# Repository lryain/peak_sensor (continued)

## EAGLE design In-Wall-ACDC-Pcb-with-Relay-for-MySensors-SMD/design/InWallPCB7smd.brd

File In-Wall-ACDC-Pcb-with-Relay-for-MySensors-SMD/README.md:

This is a PCB that uses AC power to run a MySensors node and a relay (SSR) inside a wall socket. The main goal is to have a MySensors node with I/O to be able to build your own node with your own sensors inside a normal (European) wall socket. It comes with PCB and a 3d box for protection and safety. 

This is a development of my first [In-Wall-ACDC-Pcb-for-MySensors](https://www.openhardware.io/view/13/In-Wall-ACDC-Pcb-for-MySensors) (Not SMD components, only axial)

_Note: This PCB are using SMD components!_

### Current Status and revision

Working on rev 7.1 including MysX 2.?, security improvements
Sent to PCB house 16sept, testing next.

#### Rev 7.0

- Changes in resistors and NPN transistor for relay to work better.
- Designed 3dboxes for safety.
- Increased AC-DC separation (Rev 7 = 5mm)
- AC clearance 2.5mm minimum, added millings.
- Redesigned outer dimension/border.
- Safety recommendations: This PCB meets the criteria of pollution level II (2,5mm (Basic) AC seperation and 5mm (Reinforced) AC-DC separation ) and can be used "where only non-conductive contamination occurs. However, occasional temporary conductivity must be expected as a result of moisture condensation." To be on the safe side - use a sealed case!

_For rev history, see Changes.txt_

_Note when buying through openhardware.io may say another rev. This is only revision for manufacturer, not current PCB revision. I always update PCB gerber files for sale first on openhardware.io_

### **Why??**

I designed this project for the main purpose of safely powering a node from a AC source. Battery operations and 5v phone chargers in all its glory but I needed a node small enough to put inside a wall-socket, adaptable/dynamic and AC powered. 

We have AC mains running everywhere in our houses today and this project aims for converting AC to 5vDC with safety as priority #1. 

#### Aim of this project

- Convert 240v/120v AC to 5v DC (using HLK-PM01)

- Make it safe!

- Fit inside standard [appliance box](http://www.elko.se/getfile.php/produkter/img/3/3/4944/Foto4944.jpg) / in wall

- Run MySensors node (Arduino Pro Mini, NRF24L01+, MysX Gpio for sensors)

- Have a on board relay (SSR).

- Make it as small as possible using SMD components.

### **How??**

By using this you have everything you need for a AC powered MySensors node. With MysX connector you have plenty of options both digital and analog input/outputs for you sensors. For the AC power there are both a temperature fuse, a normal fuse, and a varistor to protect your node.

I wanted the node to be dynamic (no sensor specific) - and therefore the MysX connector. Now you can add any sensor you like to the connector. Also, while at it - why not add a relay. Since Im going to use this around AC i might also be able to switch it in the same time.

Follow this thread for latest info: https://forum.mysensors.org/topic/4187/in-wall-pcb-with-relay-for-mysensors-smd

Build instructions coming soon, see BOM for more info.

### **What??**

**Power **- Using the HLK-PM01 converting AC 240/120v to 5v dc and running the MySensors node. The input is protected with a fuse, temp fuse and varistor ([read this discussion](http://forum.mysensors.org/topic/1607/safe-in-wall-ac-to-dc-transformers)).

**MySensors **- A Atmega328p-au (normal schematics) and a Nrf24l01+ SMD Radio with all the normal components.

**I/O** - MysX (Raw input not possible) + some extra (A4+A5), ICSP**

**Relay(SSR)** - A Omron G3MC-202PL protected with a fuse of your choise (axial)

**3d-box** - A part of safety, attached is a .stl file with a case for 3d printing. This can be printed in your 3d printer or sent to a 3d-hub.

### Safety

Safety is one of the most important aspects of this project! Se more here: https://forum.mysensors.org/topic/4175/clearance-creepage-and-other-safety-aspects-in-mysensors-pcbs. It is highly recommended to use the latest revision for best safety.

Text below is written for the latest posted revision. For older revisions, please see changes.txt

##### AC-DC Separation
My thoughts has been to separate AC (primary) and DC (secondary) sides completely. At this point (Rev 7.0) this separation is 6.5mm so below minimum for use outdoor (in pollution level 3 = 8.0mm) but it should be OK if you dont use in in worst case pollution. In upcoming revisions I may add millings to increase creepage. This revision i recommend using it indoors and with the 3d case (or any case!) If you put it in a completely sealed case it should be ok to use outdoor.

The HLK-PM01 has been discussed in many threads here and are transformer based so it should be safe. More about it [here ](http://lygte-info.dk/review/Power%20Mains%20to%205V%200.6A%20Hi-Link%20HLK-PM01%20UK.html)and [here](https://skippy.org.uk/quick-look-at-the-hlk-pm01/).  

Note: there has recently (Sept 16) been some [fake/pirated HLK components](https://forum.mysensors.org/topic/1607/safe-in-wall-ac-to-dc-transformers/356)! Warning!

##### AC high voltage trace creepage

As for the separation within the AC traces I have tried to use 3mm creepage and clearance but this turned out to be to hard. This PCB  (Rev 7.0) has a creepage distance on the AC side of 2.5mm. This means if you are using 240v you can put it in pollution level II Sames as above, dont use it outdoors and put it in a case.

### Disclaimer

If you order or use this you agree to and understand that the author is not liable for any injury or damage howsoever caused and that you use this PCB at your own risk. This is DIY and the author has not made any professional test. This product has not been marked with any certification marks and cant be guaranteed to compliance with any standards. 

### **Cost**?
Total cost for one node is about US$14 where the relay and HLK-pm01 is about US$10(See BOM).

### **Bonus**

You can actually cut/split the PCB between AC and DC side and get a normal 5v MySensors node where you can attach sensors to MysX connector.

##### Links

- http://forum.mysensors.org/topic/1607/safe-in-wall-ac-to-dc-transformers

- http://forum.mysensors.org/topic/1540/110v-230v-ac-to-mysensors-pcb-board

- [Performance test and review of mains to 5V 0.6A Hi-Link HLK-PM01](http://lygte-info.dk/review/Power%20Mains%20to%205V%200.6A%20Hi-Link%20HLK-PM01%20UK.html)

- https://skippy.org.uk/quick-look-at-the-hlk-pm01/

- https://www.ieee.li/pdf/essay/safety_considerations_in_power_supply_design.pdf

### Questions needing answers

- Reliability, when will it fail? (compared to a commercial product?)
- How will it fail? What is it weakest point?
- Will my safety components be enough and prevail damage... ?
- What will happen when it fails?

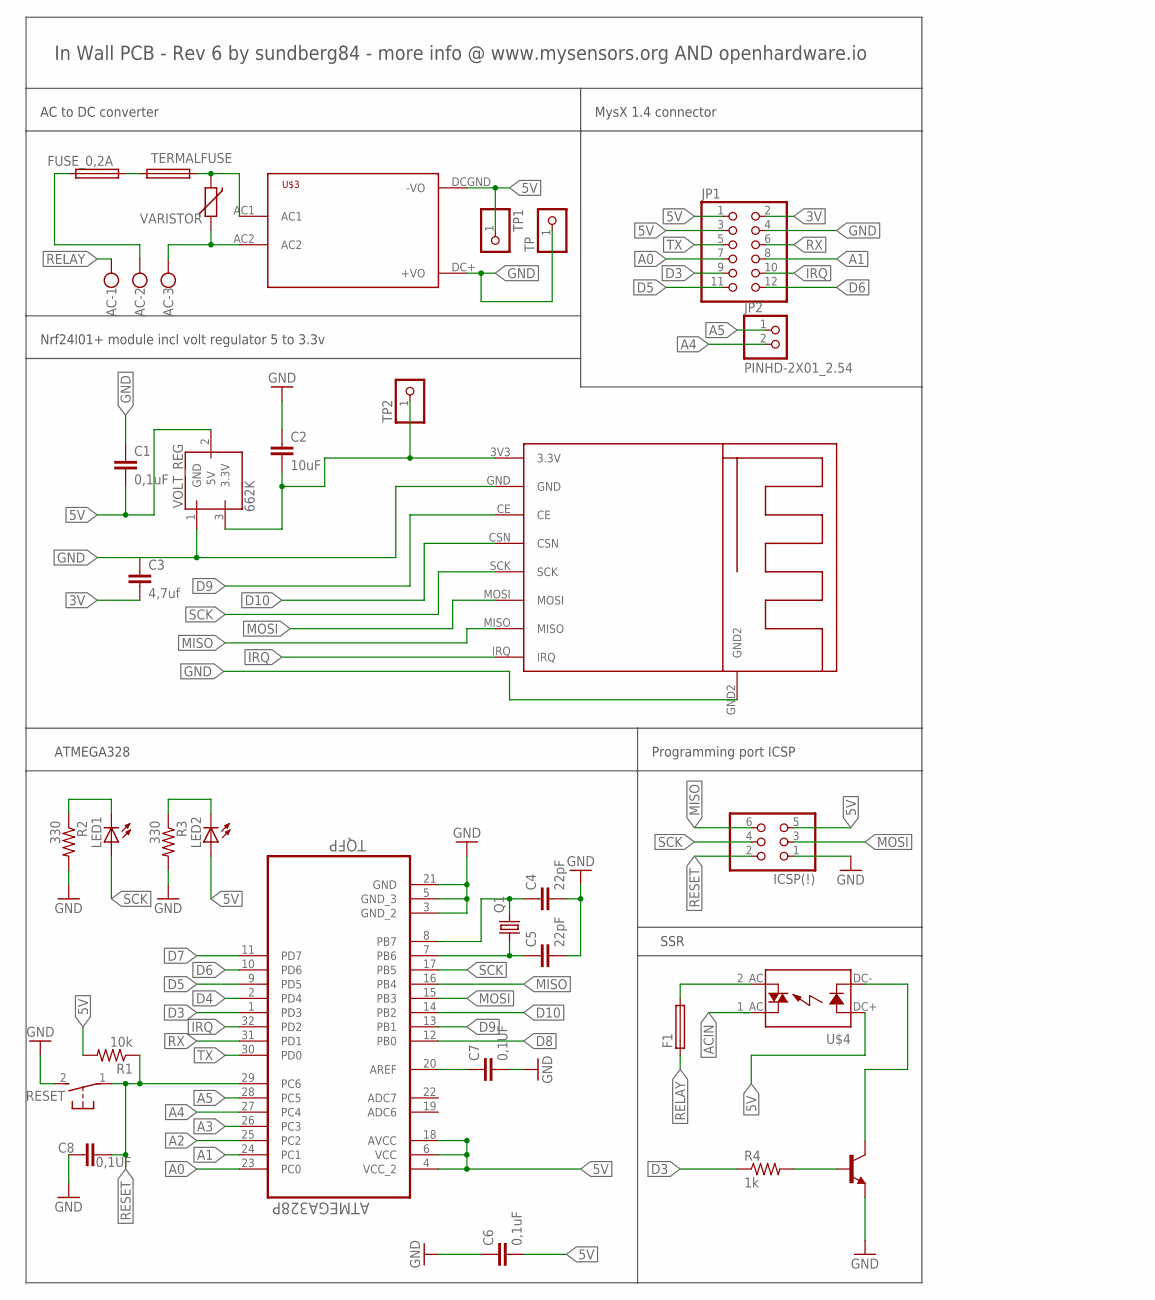
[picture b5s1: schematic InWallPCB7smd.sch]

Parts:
AC: W237-103
ATMEGA328: ATMEGA328P-AU; QFP80P900X900X120-32N
C1, C6: 0,1uF; 0805
C2: 10uF; 0805
C3: 4,7uf; 0805
C4, C5: 22pF; 0805
C7, C8: 0,1UF; 0805
F1: 19559
FUSE_0,2A: FUSETE5; TE5
ICSP(!): PINHD-2X03_2.54; 2X03
J3Y: J3Y_S8050_SMD_NPN_TRANSISTOR; SOT-23-3
JP1: PINHD-2X06_2.54; 2X06
JP2: PINHD-2X01_2.54; 2X01
LED1, LED2: LEDCHIPLED_0805; CHIPLED_0805
Q1: CRYSTALHC49S; HC49/S
R1: 10k; 0805
R2, R3: 330; 0805
R4: 1k; 0805
RESET: DTSM-3
TERMALFUSE: FUSETE5; TE5
TP, TP1, TP2: PINHD-1X1; 1X01
U$1: SMD24L01+SMD; NRF24L01+SMD
U$3: HLK-PM01
U$4: OMRON_G3MC-202PL_5V_SSR; OMRON_G3MC_202PL_5V_SSR
VARISTOR: VARISTOR-7,5; R-7,5
VOLT_REG: 662K; SOT-23-3

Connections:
3V: C2.2, C3.2, JP1.2, TP2.1, U$1.3V3 (3.3V), VOLT_REG.3 (3.3V)
5V: ATMEGA328.4 (VCC_2), ATMEGA328.6 (VCC), ATMEGA328.18 (AVCC), C1.2, C6.2, ICSP(!).5, JP1.1, JP1.3, LED2.A, R1.2, TP1.1, U$3.DCGND (-VO), U$4.DC+ (DCSIGNAL), VOLT_REG.2 (5V)
A0: ATMEGA328.23 (PC0), JP1.7
A1: ATMEGA328.24 (PC1), JP1.8
A2: ATMEGA328.25 (PC2)
A3: ATMEGA328.26 (PC3)
A4: ATMEGA328.27 (PC4), JP2.2
A5: ATMEGA328.28 (PC5), JP2.1
ACGND: AC.3, U$3.AC2, VARISTOR.2
ACIN: AC.2, FUSE_0,2A.1, U$4.1_AC (HOT)
D3: ATMEGA328.1 (PD3), JP1.9, R4.1
D4: ATMEGA328.2 (PD4)
D5: ATMEGA328.9 (PD5), JP1.11
D6: ATMEGA328.10 (PD6), JP1.12
D7: ATMEGA328.11 (PD7)
D8: ATMEGA328.12 (PB0)
D9: ATMEGA328.13 (PB1), U$1.CE
D10: ATMEGA328.14 (PB2), U$1.CSN
GND: ATMEGA328.3 (GND_2), ATMEGA328.5 (GND_3), ATMEGA328.21 (GND), C1.1, C2.1, C3.1, C4.2, C5.2, C6.1, C7.2, C8.1, ICSP(!).1, J3Y.3 (E), JP1.4, R2.2, R3.2, RESET.2, TP.1, U$1.GND, U$1.GND2, U$3.DC+ (+VO), VOLT_REG.1 (GND)
IRQ: ATMEGA328.32 (PD2), JP1.10, U$1.IRQ
MISO: ATMEGA328.16 (PB4), ICSP(!).6, U$1.MISO
MOSI: ATMEGA328.15 (PB3), ICSP(!).3, U$1.MOSI
unnamed: FUSE_0,2A.2, TERMALFUSE.2
unnamed: LED1.C, R2.1
unnamed: F1.2, U$4.2_AC (NEUTRAL)
unnamed: ATMEGA328.8 (PB7), C4.1, Q1.2
unnamed: LED2.C, R3.1
unnamed: TERMALFUSE.1, U$3.AC1, VARISTOR.1
unnamed: ATMEGA328.7 (PB6), C5.1, Q1.1
unnamed: ATMEGA328.20 (AREF), C7.1
unnamed: J3Y.1 (B), R4.2
unnamed: J3Y.2 (C), U$4.DC- (DCGND)
RELAY: AC.1, F1.1
RESET: ATMEGA328.29 (PC6), C8.2, ICSP(!).2, R1.1, RESET.1
RX: ATMEGA328.31 (PD1), JP1.6
SCK: ATMEGA328.17 (PB5), ICSP(!).4, LED1.A, U$1.SCK
TX: ATMEGA328.30 (PD0), JP1.5

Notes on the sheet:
AC to DC converter
Nrf24l01+ module incl volt regulator 5 to 3.3v
MysX 1.4 connector
In Wall PCB - Rev 6 by sundberg84 - more info @ www.mysensors.org AND openhardware.io
Programming port ICSP
ATMEGA328
SSR

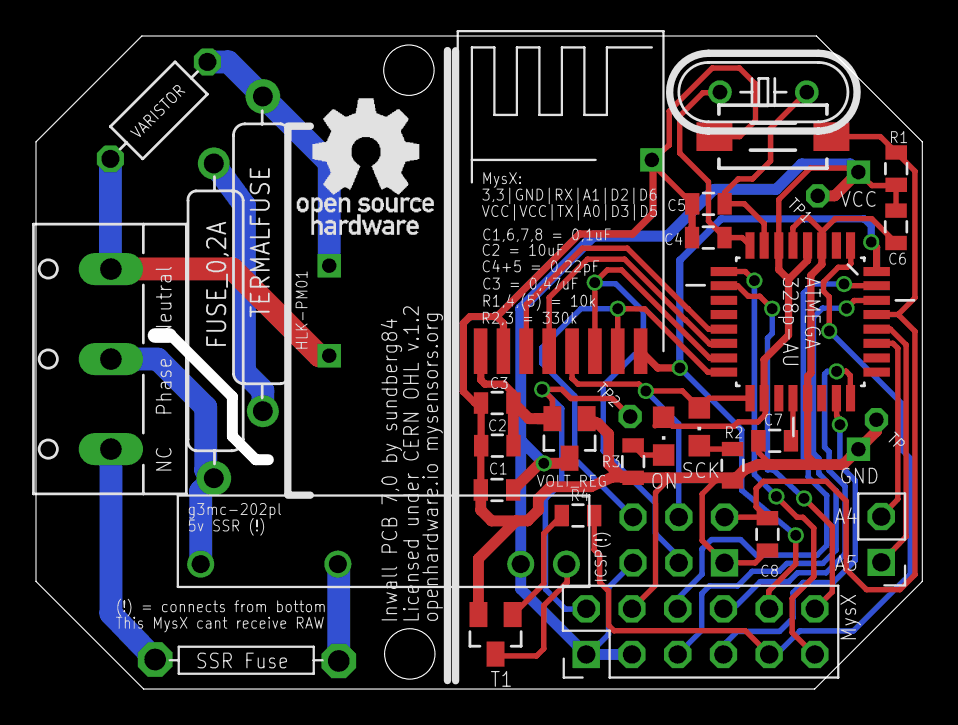
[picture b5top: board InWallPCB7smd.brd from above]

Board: 2 copper layers, 49.2 x 36.3 mm, 33 parts (1 on the bottom side), 32 nets.

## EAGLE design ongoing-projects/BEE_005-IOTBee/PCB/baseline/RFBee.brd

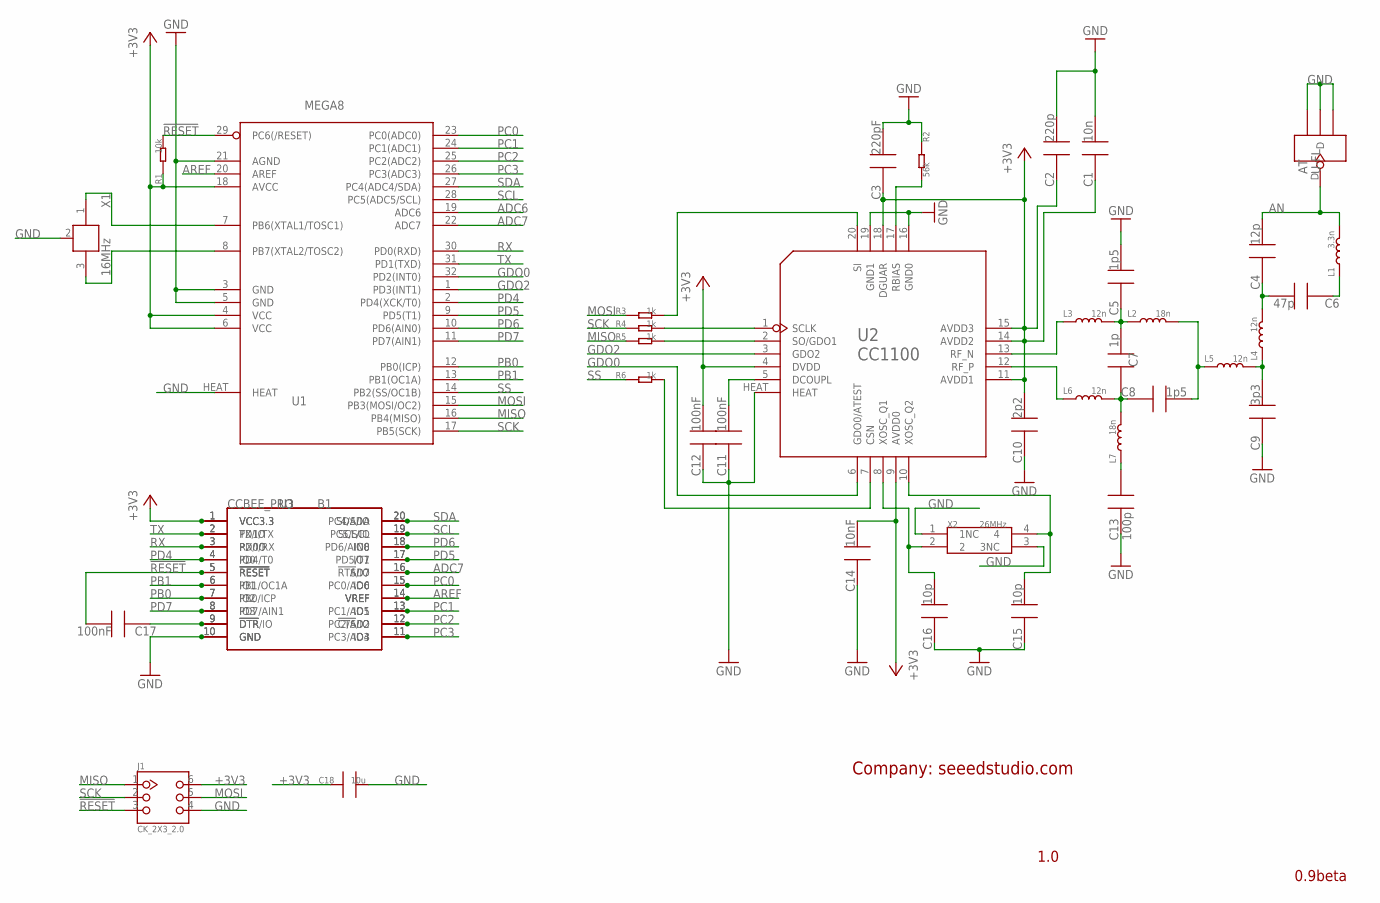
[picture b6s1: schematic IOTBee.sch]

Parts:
AT: U-FL
B1: CCBEE_PRO; CCBEE-PRO
C1: 10n; 0603_S
C2: 220p; 0603_S
C3: 220pF; 0603_S
C4: 12p; 0603_S
C5, C8: 1p5; 0603_S
C6: 47p; 0603_S
C7: 1p; 0603_S
C9: 3p3; 0603_S
C10: 2p2; 0603_S
C11, C12, C17: 100nF; 0603_S
C13: 100p; 0603_S
C14: 10nF; 0603_S
C15, C16: 10p; 0603_S
C18: 10u; 0805
J1: CK_2X3_2.0
L1: 3.3n; 0603_S
L2, L7: 18n; 0603_S
L3, L4, L5, L6: 12n; 0603_S
R1: 10k; 0603_S
R2: 56k; 0603_S
R3, R4, R5, R6: 1k; 0603_S
U1: MEGA8; MLF32X
U2: CC1100; QFN20
U3: BEE-OPENBEE-BTSMD; 20P-SMD-2.0-BT
X1: 16MHz; XTAL_3X2
X2: 26MHz; X3225

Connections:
!RESET: B1.5 (!RESET), C17.2, J1.3, R1.2, U1.29 (PC6(/RESET)), U3.5 (!RESET)
+3V3: B1.1 (VCC3.3), C1.1, C2.1, C3.1, C10.2, C12.2, C14.2, C18.1, J1.6, R1.1, U1.4 (VCC), U1.6 (VCC), U1.18 (AVCC), U2.4 (DVDD), U2.9 (AVDD0), U2.11 (AVDD1), U2.14 (AVDD2), U2.15 (AVDD3), U2.18 (DGUAR), U3.1 (VCC3.3)
ADC6: U1.19 (ADC6)
ADC7: B1.16 (AD7), U1.22 (ADC7), U3.16 (!RTS!/IO)
AN: AT.D, C4.2, L1.2
AREF: B1.14 (VREF), U1.20 (AREF), U3.14 (VREF)
DTR: B1.9 (!DTR), C17.1, U3.9 (!DTR!/IO)
GDO0: U1.32 (PD2(INT0)), U2.6 (GDO0/ATEST)
GDO2: U1.1 (PD3(INT1)), U2.3 (GDO2)
GND: AT.GND1, AT.GND2, AT.GND3, B1.10 (GND), C1.2, C2.2, C3.2, C5.2, C9.1, C10.1, C11.1, C12.1, C13.1, C14.1, C15.1, C16.1, C18.2, J1.4, R2.1, U1.3 (GND), U1.5 (GND), U1.21 (AGND), U1.HEAT, U2.16 (GND0), U2.19 (GND1), U2.HEAT, U3.10 (GND), X1.2 (GND), X2.1 (1NC), X2.3 (3NC)
MISO: J1.1, R5.1, U1.16 (PB4(MISO))
MOSI: J1.5, R3.1, U1.15 (PB3(MOSI/OC2))
unnamed: C11.2, U2.5 (DCOUPL)
unnamed: C16.2, U2.8 (XOSC_Q1), X2.2
unnamed: R4.2, U2.1 (SCLK)
unnamed: L3.1, U2.13 (RF_N)
unnamed: L6.1, U2.12 (RF_P)
unnamed: C5.1, C7.2, L2.1, L3.2
unnamed: C7.1, C8.1, L6.2, L7.2
unnamed: C8.2, L2.2, L5.1
unnamed: C9.2, L4.1, L5.2
unnamed: C4.1, C6.2, L4.2
unnamed: U1.7 (PB6(XTAL1/TOSC1)), X1.1
unnamed: C13.2, L7.1
unnamed: U1.8 (PB7(XTAL2/TOSC2)), X1.3 (2)
unnamed: R3.2, U2.20 (SI)
unnamed: R2.2, U2.17 (RBIAS)
unnamed: C15.2, U2.10 (XOSC_Q2), X2.4
unnamed: R5.2, U2.2 (SO/GDO1)
unnamed: R6.2, U2.7 (CSN)
unnamed: C6.1, L1.1
PB0: B1.7 (PB0/ICP), U1.12 (PB0(ICP)), U3.7 (IO2)
PB1: B1.6 (PB1/OC1A), U1.13 (PB1(OC1A)), U3.6 (IO1)
PC0: B1.15 (PC0/AD0), U1.23 (PC0(ADC0)), U3.15 (IO6)
PC1: B1.13 (PC1/AD1), U1.24 (PC1(ADC1)), U3.13 (IO5)
PC2: B1.12 (PC2/AD2), U1.25 (PC2(ADC2)), U3.12 (!CTS!/IO)
PC3: B1.11 (PC3/AD3), U1.26 (PC3(ADC3)), U3.11 (IO4)
PD4: B1.4 (PD4/T0), U1.2 (PD4(XCK/T0)), U3.4 (IO0)
PD5: B1.17 (PD5/T1), U1.9 (PD5(T1)), U3.17 (IO7)
PD6: B1.18 (PD6/AIN0), U1.10 (PD6(AIN0)), U3.18 (IO8)
PD7: B1.8 (PD7/AIN1), U1.11 (PD7(AIN1)), U3.8 (IO3)
RX: B1.3 (PD0/RX), U1.30 (PD0(RXD)), U3.3 (RX/IO)
SCK: J1.2, R4.1, U1.17 (PB5(SCK))
SCL: B1.19 (PC5/SCL), U1.28 (PC5(ADC5/SCL)), U3.19 (SCL/IO)
SDA: B1.20 (PC4/SDA), U1.27 (PC4(ADC4/SDA)), U3.20 (SDA/IO)
SS: R6.1, U1.14 (PB2(SS/OC1B))
TX: B1.2 (PD1/TX), U1.31 (PD1(TXD)), U3.2 (TX/IO)

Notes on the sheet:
0.9beta
1.0
Company: seeedstudio.com

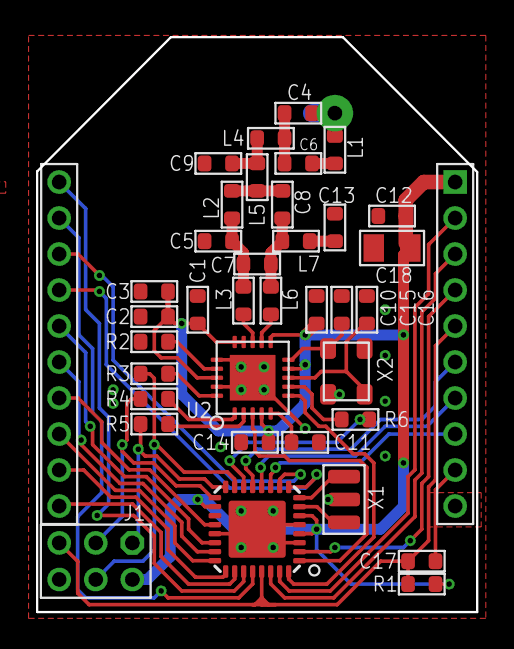
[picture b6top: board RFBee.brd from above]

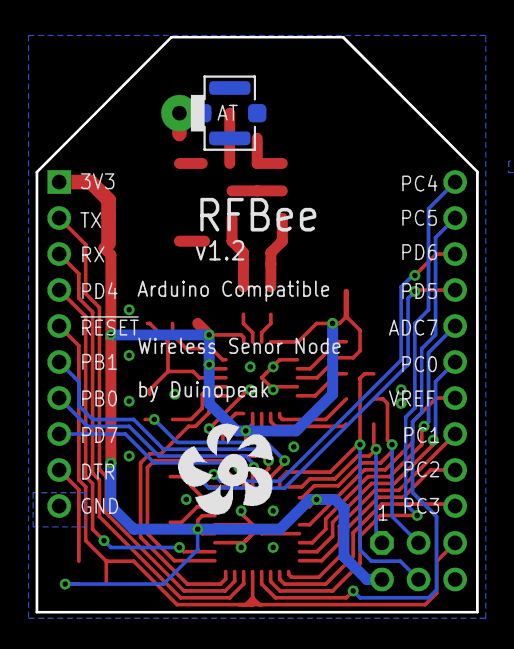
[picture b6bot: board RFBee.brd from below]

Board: 2 copper layers, 24.4 x 31.9 mm, 39 parts (3 on the bottom side), 46 nets.

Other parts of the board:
U$1: DUINOFUN-LOGO-PCB-0.7

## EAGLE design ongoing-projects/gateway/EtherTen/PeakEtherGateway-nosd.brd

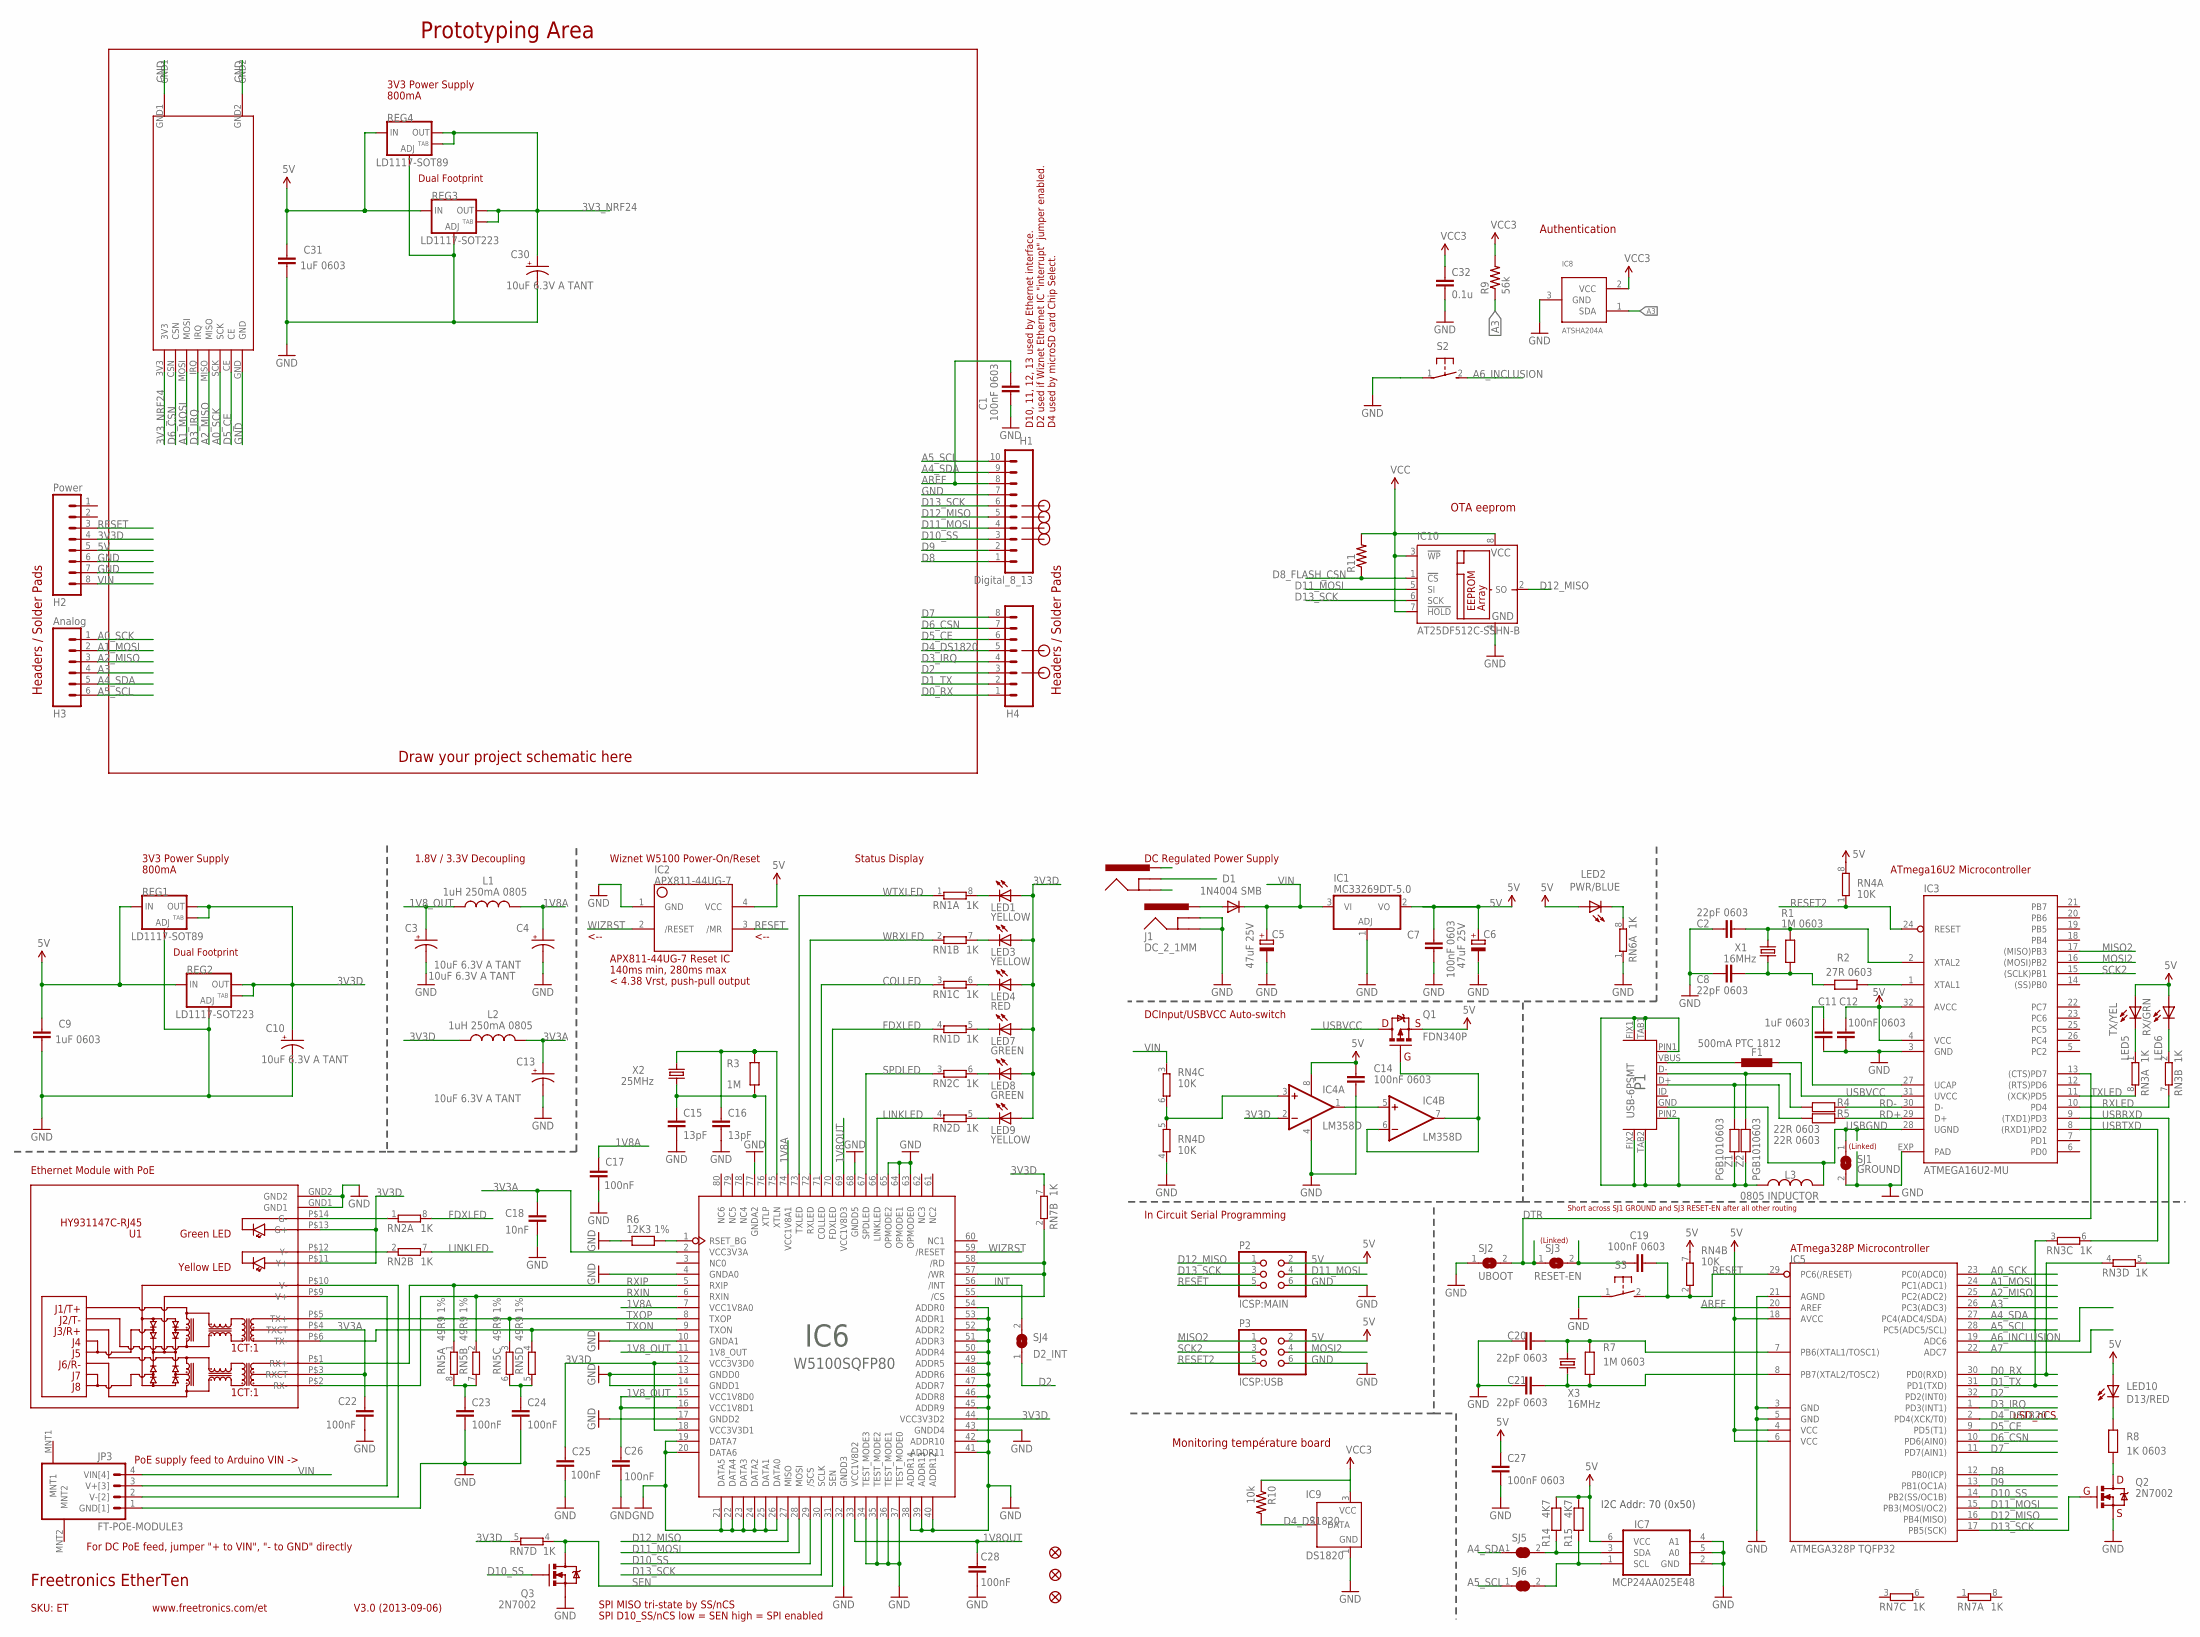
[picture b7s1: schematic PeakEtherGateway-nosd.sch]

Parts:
C1, C7, C12, C14, C19, C27: 100nF 0603; 0603
C2, C8, C20, C21: 22pF 0603; 0603
C3, C4, C10, C13, C30: 10uF 6.3V A TANT; EIA3216
C5, C6: 47uF 25V; PANASONIC_D
C9, C11, C31: 1uF 0603; 0603
C15, C16: 13pF; 0603
C17, C22, C23, C24, C25, C26, C28: 100nF; 0603
C18: 10nF; 0603
C32: 0.1u; 0603-CAP
D1: 1N4004 SMB; SMB-DIODE
F1: 500mA PTC 1812; L1812
FID1, FID2, FID3: FIDUCIAL1X2.5; FIDUCIAL-1X2.5
H1: Digital_8_13; 1X10
H2: Power; 1X08
H3: Analog; 1X06
H4: Digital_0_7; 1X08
IC1: MC33269DT-5.0; DPACK
IC2: APX811-44UG-7; SOT143-R
IC3: ATMEGA16U2-MU; ATMEL_QFN32
IC4: LM358D; SO08
IC5: ATMEGA328P TQFP32; TQFP32-08
IC6: W5100SQFP80; SQFP80
IC7: MCP24AA025E48; SOT23-6
IC8: ATSHA204A; SOT23
IC9: DS1820; TO92-
IC10: AT25DF512C-SSHN-B; SO-08
J1: DC_2_1MM; POWER_JACK_PTH
J2: POWER_JACKOVERPASTE_REDBOARD_0603; POWER_JACK_SMD_OVERPASTE_REDBOARD_0603
JP3: FT-POE-MODULE3; FT-POE-MODULE-NOLABEL
L1, L2: 1uH 250mA 0805; L2012C
L3: 0805 INDUCTOR; 0805-LARGE
LED1, LED3, LED9: YELLOW; LED-0603
LED2: PWR/BLUE; LED-0603
LED4: RED; LED-0603
LED5: TX/YEL; LED-0603
LED6: RX/GRN; LED-0603
LED7, LED8: GREEN; LED-0603
LED10: D13/RED; LED-0603
P1: USB-6PSMT; USB-MICROB-MB05PMXX
P2: ICSP:MAIN; 2X03
P3: ICSP:USB; 2X03
Q1: FDN340P; SOT23
Q2, Q3: 2N7002; SOT23-3
R1, R7: 1M 0603; 0603
R2: 27R 0603; 0603
R3: 1M; 0603
R4, R5: 22R 0603; 0603
R6: 12K3 1%; 0603
R8: 1K 0603; 0603
R9: 56k; 0603-RES
R10: 10k; 0603-RES
R11: RESISTOR0603-RES; 0603-RES
R14, R15: 4K7; 0603
REG1, REG4: LD1117-SOT89; SOT89
REG2, REG3: LD1117-SOT223; SOT223
RN1, RN2, RN3, RN6, RN7: 1K; CAY16
RN4: 10K; CAY16
RN5: 49R9 1%; CAY16
S2, S3: 31-XX; B3F-31XX
SJ1: GROUND; SJ
SJ2: UBOOT; SJ
SJ3: RESET-EN; SJ
SJ4: D2_INT; SJ
SJ5, SJ6: SJCN; SJC
U1: HY931147C-RJ45; HY931147C
U$17: NRF2401; NRF2401_PA_OUTLINE
X1, X3: 16MHz; HC49U-V
X2: 25MHz; HC49U-V
Z1, Z2: PGB1010603; 0603

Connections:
1V8A: C4.A (+), C17.1, IC6.7 (VCC1V8A0), IC6.74 (VCC1V8A1), L1.2
1V8OUT: C28.1, IC6.33 (VCC1V8D2), IC6.69 (VCC1V8D3)
1V8_OUT: C3.A (+), C26.1, IC6.11 (1V8_OUT), IC6.15 (VCC1V8D0), IC6.16 (VCC1V8D1), L1.1
3V3A: C13.A (+), C18.1, C22.1, IC6.2 (VCC3V3A), L2.2, U1.P$3 (RXCT), U1.P$4 (TXCT)
3V3D: C10.A (+), C25.1, H2.4, IC4.2 (-IN), IC6.12 (VCC3V3D0), IC6.18 (VCC3V3D1), IC6.44 (VCC3V3D2), L2.1, LED1.A, LED3.A, LED4.A, LED7.A, LED8.A, LED9.A, REG1.2 (OUT), REG1.4 (OUT), REG2.2 (OUT), REG2.4 (OUT), RN7.5 (2), RN7.7 (2), U1.P$11 (Y+), U1.P$13 (G+)
3V3_NRF24: C30.A (+), C32.1, IC8.2 (VCC), IC9.3 (VCC), IC10.3 (!WP), IC10.7 (!HOLD), IC10.8 (VCC), R9.2, R10.1, R11.2, REG3.2 (OUT), REG3.4 (OUT), REG4.2 (OUT), REG4.4 (OUT), U$17.3V3
5V: C6.+, C7.1, C9.1, C12.1, C14.1, C27.1, C31.1, H2.5, IC1.2 (VO), IC2.4 (VCC), IC3.4 (VCC), IC3.32 (AVCC), IC4.8 (V+), IC5.4 (VCC), IC5.6 (VCC), IC5.18 (AVCC), IC7.6 (VCC), LED2.A, LED5.A, LED6.A, LED10.A, P2.2, P3.2, Q1.2 (S), R14.1, R15.1, REG1.3 (IN), REG2.3 (IN), REG3.3 (IN), REG4.3 (IN), RN4.7 (2), RN4.8 (2)
A0_SCK: H3.1, IC5.23 (PC0(ADC0)), U$17.SCK
A1_MOSI: H3.2, IC5.24 (PC1(ADC1)), U$17.MOSI
A2_MISO: H3.3, IC5.25 (PC2(ADC2)), U$17.MISO
A3: H3.4, IC5.26 (PC3(ADC3)), IC8.1 (SDA), R9.1
A4_SDA: H1.9, H3.5, IC5.27 (PC4(ADC4/SDA)), SJ5.1
A5_SCL: H1.10, H3.6, IC5.28 (PC5(ADC5/SCL)), SJ6.1
A6_INCLUSION: IC5.19 (ADC6), S2.2 (S)
A7: IC5.22 (ADC7)
AREF: C1.1, H1.8, IC5.20 (AREF)
COLLED: IC6.71 (COLLED), RN1.3 (1)
D0_RX: H4.1, IC5.30 (PD0(RXD)), RN3.4 (1)
D1_TX: H4.2, IC5.31 (PD1(TXD)), RN3.3 (1)
D2: H4.3, IC5.32 (PD2(INT0)), SJ4.1
D3_IRQ: H4.4, IC5.1 (PD3(INT1)), U$17.IRQ
D4_DS1820: H4.5, IC5.2 (PD4(XCK/T0)), IC9.2 (DATA), R10.2
D5_CE: H4.6, IC5.9 (PD5(T1)), U$17.CE
D6_CSN: H4.7, IC5.10 (PD6(AIN0)), U$17.CSN
D7: H4.8, IC5.11 (PD7(AIN1))
D8: H1.1, IC5.12 (PB0(ICP))
D8_FLASH_CSN: IC10.1 (!CS), R11.1
D9: H1.2, IC5.13 (PB1(OC1A))
D10_SS: H1.3, IC5.14 (PB2(SS/OC1B)), IC6.29 (/SCS), Q3.1 (G)
D11_MOSI: H1.4, IC5.15 (PB3(MOSI/OC2)), IC6.28 (MOSI), IC10.5 (SI), P2.4
D12_MISO: H1.5, IC5.16 (PB4(MISO)), IC6.27 (MISO), IC10.2 (SO), P2.1
D13_SCK: H1.6, IC5.17 (PB5(SCK)), IC6.30 (SCLK), IC10.6 (SCK), P2.3, Q2.1 (G)
DTR: IC3.13 ((CTS)PD7), SJ2.2, SJ3.1
FDXLED: IC6.70 (FDXLED), RN1.4 (1), RN2.8 (2)
GND: C1.2, C2.1, C3.C (-), C4.C (-), C5.-, C6.-, C7.2, C8.1, C9.2, C10.C (-), C11.2, C12.2, C13.C (-), C14.2, C15.2, C16.2, C17.2, C18.2, C20.1, C21.1, C22.2, C23.2, C24.2, C25.2, C26.2, C27.2, C28.2, C30.C (-), C31.2, C32.2, H1.7, H2.6, H2.7, IC1.1 (ADJ), IC2.1 (GND), IC3.3 (GND), IC3.EXP (PAD), IC4.4 (V-), IC5.3 (GND), IC5.5 (GND), IC5.21 (AGND), IC6.4 (GNDA0), IC6.10 (GNDA1), IC6.13 (GNDD0), IC6.14 (GNDD1), IC6.17 (GNDD2), IC6.19 (DATA7), IC6.20 (DATA6), IC6.21 (DATA5), IC6.22 (DATA4), IC6.23 (DATA3), IC6.24 (DATA2), IC6.25 (DATA1), IC6.26 (DATA0), IC6.32 (GNDD3), IC6.34 (TEST_MODE3), IC6.35 (TEST_MODE2), IC6.36 (TEST_MODE1), IC6.37 (TEST_MODE0), IC6.38 (ADDR14), IC6.39 (ADDR13), IC6.40 (ADDR12), IC6.41 (ADDR11), IC6.42 (ADDR10), IC6.43 (GNDD4), IC6.45 (ADDR9), IC6.46 (ADDR8), IC6.47 (ADDR7), IC6.48 (ADDR6), IC6.49 (ADDR5), IC6.50 (ADDR4), IC6.51 (ADDR3), IC6.52 (ADDR2), IC6.53 (ADDR1), IC6.54 (ADDR0), IC6.63 (OPMODE0), IC6.64 (OPMODE1), IC6.65 (OPMODE2), IC6.68 (GNDD5), IC6.77 (GNDA2), IC7.2 (GND), IC7.4 (A1), IC7.5 (A0), IC8.3 (GND), IC9.1 (GND), IC10.4 (GND), J1.GND, J1.GNDBREAK, JP3.1 (GND[1]), P2.6, P3.6, Q2.2 (S), Q3.2 (S), R6.1, REG1.1 (ADJ), REG2.1 (ADJ), REG3.1 (ADJ), REG4.1 (ADJ), RN4.4 (1), RN6.1, S2.1, S3.1, SJ1.2, SJ2.1, U1.GND1, U1.GND2, U$17.GND
GND1: J2.GND (GNDBREAK)
INSERT: J2.P$4 (GND)
INT: IC6.56 (/INT), SJ4.2
LINKLED: IC6.66 (LINKLED), RN2.4 (1), RN2.7 (2)
MISO2: IC3.17 ((MISO)PB3), P3.1
MOSI2: IC3.16 ((MOSI)PB2), P3.4
unnamed: C24.1, RN5.5 (2), RN5.6 (2)
unnamed: C20.2, IC5.7 (PB6(XTAL1/TOSC1)), R7.2, X3.2
unnamed: C19.1, SJ3.2
unnamed: LED10.C, R8.2
unnamed: IC7.1 (SCL), R15.2, SJ6.2
unnamed: Q2.3 (D), R8.1
unnamed: C21.2, IC5.8 (PB7(XTAL2/TOSC2)), R7.1, X3.1
unnamed: IC3.1 (XTAL1), R2.1
unnamed: L3.1, P1.FIX1, P1.FIX2, P1.PIN1, P1.PIN2, P1.TAB1, P1.TAB2, Z1.2, Z2.2
unnamed: LED6.C, RN3.2 (1)
unnamed: IC4.3 (+IN), RN4.5 (2), RN4.6 (2)
unnamed: LED5.C, RN3.1
unnamed: LED2.C, RN6.8 (2)
unnamed: P1.D+, R5.2, Z1.1
unnamed: P1.D-, R4.2, Z2.1
unnamed: IC4.6 (-IN), IC4.7 (OUT), Q1.1 (G)
unnamed: IC4.1 (OUT), IC4.5 (+IN)
unnamed: LED8.C, RN2.6 (2)
unnamed: IC6.55 (/CS), IC6.57 (/WR), IC6.58 (/RD), RN7.2 (1)
unnamed: LED9.C, RN2.5 (2)
unnamed: IC7.3 (SDA), R14.2, SJ5.2
unnamed: D1.A, J1.PWR
unnamed: RN2.1, U1.P$14 (G-)
unnamed: JP3.3 (V+[3]), U1.P$9 (V+)
unnamed: JP3.2 (V-[2]), U1.P$10 (V-)
unnamed: C2.2, IC3.2 (XTAL2), R1.2, X1.2
unnamed: C8.2, R1.1, R2.2, X1.1
unnamed: F1.1, P1.VBUS
unnamed: C11.1, IC3.27 (UCAP)
unnamed: C23.1, RN5.7 (2), RN5.8 (2)
unnamed: IC6.1 (RSET_BG), R6.2
unnamed: LED7.C, RN1.5 (2)
unnamed: LED4.C, RN1.6 (2)
unnamed: LED3.C, RN1.7 (2)
unnamed: LED1.C, RN1.8 (2)
unnamed: RN2.2 (1), U1.P$12 (Y-)
PWRIN: J2.VIN0 (PWR)
RD+: IC3.29 (D+), R5.1
RD-: IC3.30 (D-), R4.1
RESET: C19.2, H2.3, IC2.3 (/MR), IC5.29 (PC6(/RESET)), P2.5, RN4.2 (1), S3.2 (S)
RESET2: IC3.24 (RESET), P3.5, RN4.1
RXIN: IC6.6 (RXIN), RN5.2 (1), U1.P$2 (RX-)
RXIP: IC6.5 (RXIP), RN5.1, U1.P$1 (RX+)
RXLED: IC3.10 (PD4), RN3.7 (2)
SCK2: IC3.15 ((SCLK)PB1), P3.3
SEN: IC6.31 (SEN), Q3.3 (D), RN7.4 (1)
SPDLED: IC6.67 (SPDLED), RN2.3 (1)
TXLED: IC3.11 ((XCK)PD5), RN3.8 (2)
TXON: IC6.9 (TXON), RN5.4 (1), U1.P$6 (TX-)
TXOP: IC6.8 (TXOP), RN5.3 (1), U1.P$5 (TX+)
USBGND: IC3.28 (UGND), L3.2, P1.GND, SJ1.1
USBRXD: IC3.9 ((TXD1)PD3), RN3.5 (2)
USBTXD: IC3.8 ((RXD1)PD2), RN3.6 (2)
USBVCC: F1.2, IC3.31 (UVCC), Q1.3 (D)
VIN: C5.+, D1.C, H2.8, IC1.3 (VI), JP3.4 (VIN[4]), RN4.3 (1)
WIZRST: IC2.2 (/RESET), IC6.59 (/RESET)
WRXLED: IC6.72 (RXLED), RN1.2 (1)
WTXLED: IC6.73 (TXLED), RN1.1
XTLN: C16.1, IC6.75 (XTLN), R3.2, X2.2
XTLP: C15.1, IC6.76 (XTLP), R3.1, X2.1

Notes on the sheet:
Prototyping Area
SKU: ET
3V3 Power Supply
Status Display
Headers / Solder Pads
Dual Footprint
1.8V / 3.3V Decoupling
Draw your project schematic here
D10, 11, 12, 13 used by Ethernet interface.
D2 used if Wiznet Ethernet IC "interrupt" jumper enabled.
PoE supply feed to Arduino VIN ->
SPI MISO tri-state by SS/nCS
SPI D10_SS/nCS low = SEN high = SPI enabled
For DC PoE feed, jumper "+ to VIN", "- to GND" directly
DC Regulated Power Supply
ATmega328P Microcontroller
APX811-44UG-7 Reset IC
140ms min, 280ms max
ATmega16U2 Microcontroller
DCInput/USBVCC Auto-switch
Wiznet W5100 Power-On/Reset
uSD_nCS
800mA
In Circuit Serial Programming
Freetronics EtherTen
V3.0 (2013-09-06)
www.freetronics.com/et
Ethernet Module with PoE
< 4.38 Vrst, push-pull output
<--
D4 used by microSD card Chip Select.
(Linked)
Short across SJ1 GROUND and SJ3 RESET-EN after all other routing
I2C Addr: 70 (0x50)
Authentication
Monitoring température board
OTA eeprom

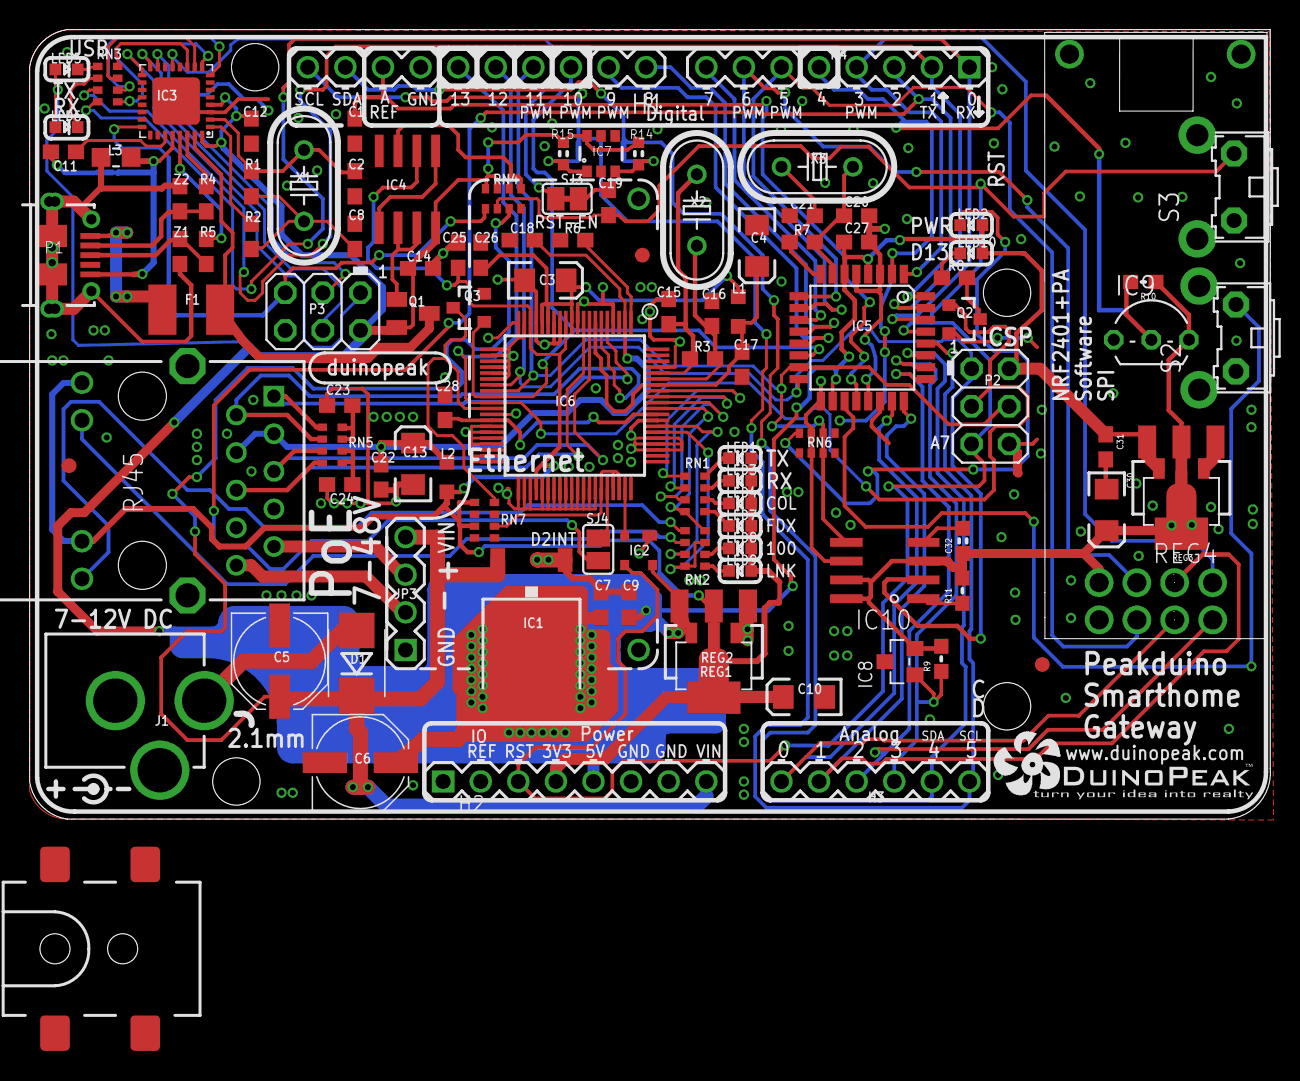
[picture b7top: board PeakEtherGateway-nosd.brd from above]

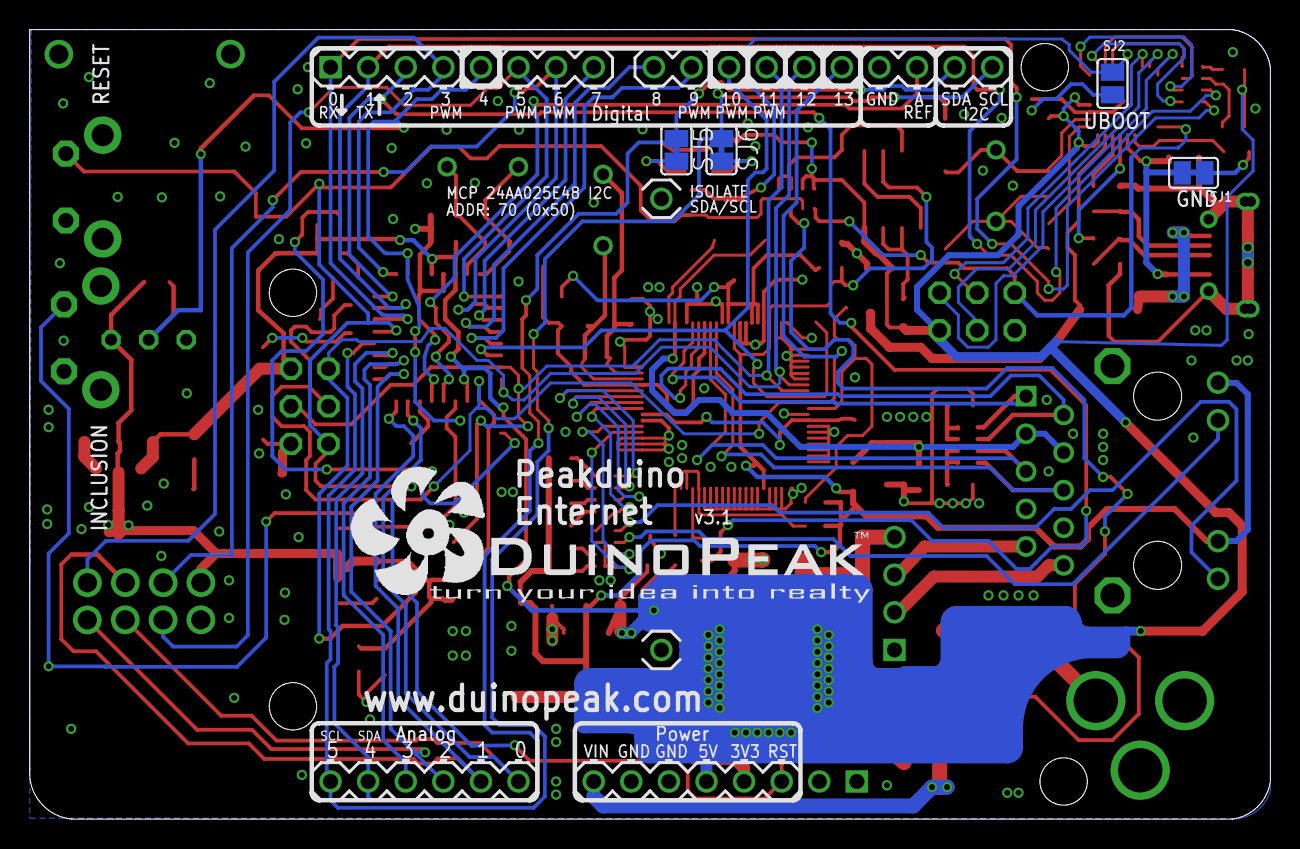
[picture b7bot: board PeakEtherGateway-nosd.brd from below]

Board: 2 copper layers, 83.8 x 53.3 mm, 113 parts (5 on the bottom side), 97 nets.

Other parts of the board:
U$8: DUINOPEAK-LOGO-1.2
U$20: DUINOPEAK-LOGO-0.6

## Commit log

2016-12-18 refactory
2017-01-20 datasheet
